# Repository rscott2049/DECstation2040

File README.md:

# DECstation 2040

## 1.0 Introduction

This document outlines the DECstation 2040, a RP2040 based DECstation 3000
emulator that can run DECWindows. A summary of features:

Hardware:

- RP2040, running at 1.8v/300 MHz
- 32 MB of PSRAM
- 8 MB SPI flash
- uSD card socket
- Monochrome VGA at 1024 x 864
- Ethernet RMII PHY support (socket on rev 1.5, integrated in rev 2.1)

Software:

- 4 port PSRAM PIO engine
- PIO driven VGA, with seperate 16x16 cursor plane overlay
- USB HID to DECWindows keyboard and mouse
  
## 1.1 Software 

### PIO:
The PSRAM/HyperRAM PIO engine provides 42/32 MB/s (write/read) of memory
bandwidth. Further, four PIO engines are used to provide four seperate
read/write memory ports. This allows independent memory access for
the emulated CPU, video DMA, and receive/send Ethernet traffic. Note that
all 32 instruction slots are used.

The video PIO engine can support up to a sysclk/2 pixel rate. Thus,
for the 300 MHz sysclk typically used, it is possible to run 1080p60 at
a pixel rate of 148.5 MHz. The default video rate is 1024 x 768 @ 70Hz,
as this matches the screen used for development and the pixel rate
is an integral divisor from sysclk. Only five PIO instruction slots are
used.

### DMA:
To drive the video PIO engine, five DMA channels are used. They are allocated
as follows:

- ctrl_dma_chan - points to DMA channel command packets
- data_dma_chan - executes DMA command packets
- ps_read_chan - points to PSRAM read data buffer
- inc_dma_chan - used to generate loop counter indices
- cur_inc_dma_chan - used as cursor loop counter

This project uses the RP2040 DMA sniffer to dynamically generate PSRAM
addresses, which eliminates the need to have a per-line PSRAM command packet. 
Further, it uses the inc_dma_chan to enable DMA command loops, eliminating
per-line DMA commands needed to send commands to the PIO pixel and PSRAM
PIO engines. This makes the amount of memory needed to drive video
independent of the display format. Currently, 86 DMA command packets are
used vs. approximately 2250 required for 1080p if a per-line DMA structure
was used.

In order to eliminate the latency from when the PSRAM PIO engine FIFO
has read data, and its delivery to SRAM, we use the ps_read_chan. This
channel is chained to after a PSRAM DMA command is executed. Without
this channel, the PSRAM PIO engine FIFO would be not be emptied until
the next DMA command is executed. This impacts the non-video PSRAM
channels, as they must wait unitl the video PSRAM command is complete.

### USB:
The USB HID code supports (at least) two keyboard/mouse combo types:
Rii mini X1 (model: RT-MWK01), purchased at MicroCenter, and Logitech
K830. 

### Emulator:
Dmitry's code at http://dmitry.gr/?r=05.Projects&proj=33.%20LinuxCard was
modified to support the RP2040, as well as adding support for video and USB
mouse/keyboard input. With overclocking and running the assembly language
version of the CPU emulator, Dmitry's Linux image reports a BOGOMIPS rating
of 13.44.

# 2.0) Getting started

## 2.1) Hardware
Build either rev 1.5 or 2.1, using the appropriate emu_brd directory. Please
note that rev 2.1 is still undergoing Ethernet debug, and has exhibited
significant packet drops. I use JLCPCB for board fabrication, and there are 
Digikey BOM spreadsheets in doc/bom. Recommend building two boards: one to
use as a 1.8v CMSIS debugger, and the other as the target. Feel free to only
populate the RP2040 related components on the CMSIS debugger.

The surface mount parts aren't too troublesome - I find the PSRAM BGA to be
much easier to solder than the RP2040 QFN. My technique is to use a hot-air
SMT rework tool. Recommended assembly steps:
1) Solder the voltage regulator, check for 1.8v and 3.3v when done.
2) Solder all of the passives, the RP2040, flash, and the USB connectors
if building rev 2.1. (Note that two bodge wires are needed to connect J5
and J11 D+/D- as my assumption that USB-A could serve as non-host connector
was incorrect).
When done, use blink_bringup (below) to check connections. (Edit blink.c
to enable the pins to check).
3) Solder the HyperRAM chip, run mem_test to check connections.
4) Solder the voltage translator chips, edit blink.c and run to check
connections.
5) Solder the connectors.

For rev 1.5:
Needs modified waveshare LAN8722 board. In addition to the modifications
outlined at: https://github.com/maximeborges/pico-rmii-ethernet, pin 13 of
the 7 x 2 connector (originally NC) is used as VDDIO for the LAN8722 chip.
To make this modification, cut the existing connection between LAN8722 pin
9 to 3.3v, and route pin 9 to pin 13 of the connector. This allows the use
of 1.8v I/O from the DECstation 2040 board. Also needed is a 6 pin header
to VGA connector. See rev 2.1 schematic for VGA pins needed.

## 2.2) Software
Start with:
http://dmitry.gr/?r=05.Projects&proj=33.%20LinuxCard
Download the images, particularly the ultrix.gui image. This should be placed
on a FAT32 for uMIPS. Edit uc_main.c to select which image to run.

Next, go to where this README.md is stored. Then set current directory to sw.
Edit the "source_this" file to reflect the location of the Pico SDK, and source
this file to set the PICO_SDK environment variable for the current session.

A good place to start is with the blink_bringup directory. CD to this,
and do:

`cmake -B build -S .`

Build software via

`./build.sh`

This will generate an .elf file in build/src. Use picotool to load this onto
the target board. After rebooting, should get "hello, world" on USB serial, as
well as on the hardware serial port. A 500 Hz square wave should be present
on GPIO21 (ret_clk). This can be changed via editing the src/blink.c file.
I use this tool incrementally while soldering the board, to verify connectivity.

Next, build the CMSIS debugger. CD to the picoprobe directory and
build with:

`cmake -B build -DCUSTOMPROBE=1
make -C build`

Program with

`sudo picotool load build/customprobe.elf`

Now go to the psram directory and do:

`cmake -B build -S .`

Build software via

`./build.sh`

This will generate most of the available packages. Of interest are:

- mem_test - a simple memory tester
- fb_test - test program for the frame buffer library
- fb_mem_test - memory test with frame buffer enabled
- pico-rv32ima - RISC-V linux emulation
- uMIPS - DECstation emulation
- pico_rmii_ethernet_httpd - test program for RMII. 

There are shell scripts to load the above:

- cl_sram.sh   - sd command line
- eth_sram.sh  - ethernet test
- fb_flash.sh  - framebuffer library test, run from flash
- fb_sram.sh   - framebuffer library test, run from SRAM
- fbm_flash.sh - memory test with framebuffer enabled, run from flash
- fbm_sram.sh  - memory test with framebuffer enabled, run from SRAM
- mt_sram.sh   - memory test, run from SRAM
- mt_flash.sh  - memory test, run from flash
- um_flash.sh - uMIPS emulator, run from flash
- um_sram.sh  - uMIPS emulator, run from SRAM

Running the code:
Connect the debugger board to the SWD port on the target.
Start the CMSIS debugger via sw/start_cmsis.sh.
Execute one of the scripts above. This will load the program into RP2040
SRAM and start it.

If you wish to run from flash, comment out the no_flash line in the source CMakeLists.txt. Note that the uMIPS emulator requires "copy_to_ram" to be enabled
when running from flash.

# 3.0) Commentary

This project has been a voyage of discovery. The first doc/build_log.txt entry
was on 23-mar-2023, but I'd been thinking of building a business card
ever since I'd read Dmitry's LinuxCard web page. I've learned how to
use the RP2040 PIO engines and the DMA subsystem to push pixels. I'm
amazed at how flexible and capable the RP2040 has turned out to be. Hats off
to the RP2040 designers! 

Most enjoyable moments:

- When the PSRAM PIO engine finally ran the memory test overnight.
- When the second solution to the problem of how to get the DMA subsytem
to do a counted loop actually worked without killing SD card access.
- When the DMA cursor read data during blanking worked, giving smooth
cursor movement.

Less than enjoyable moments:

- Realizing the "optimization" of reordering data on the PSRAM to improve
layout was wrong, after submitting the design to JLCPCB.
-  Realizing that the first flash part chosen didn't support "Continuous Read
Mode". On the other hand, this did force me to learn how to do SRAM builds,
speeding up development.
- Having the wrong footprint for the level translator on rev 1.3.
- Finding out that Digikey no longer stocked the Ethernet connector on
rev 2.0, after submitting PCB. Related - the PSRAM was out of stock, so
clicked on the recommended alternative. Was disappointed when the box
showed up, and it was the waferscale part. Tiny, but unsolderable.

# 4.0) Next steps
- Use the ps_get_buf DMA subroutine to setup the cursor PSRAM command. This
will reduce the memory footprint.
- Write the lance Ethernet emulation code for uMIPS.
- Port MicroMac https://axio.ms/projects/2024/06/16/MicroMac.html

# 5.0) Acknowledgements

This project would not exist without Dmitry's excellent LinuxCard project,
at: http://dmitry.gr/?r=05.Projects&proj=33.%20LinuxCard

Inspiration and software framework:
https://github.com/Wren6991/PicoDVI.git

DEC mouse and keyboard support used code from:
https://hackaday.io/project/19576-dec-mouse-adapter and 
https://github.com/pkoning2/lk201emu.git

Ethernet:
https://github.com/maximeborges/pico-rmii-ethernet

Also, Hackaday.com for articles on SMT soldering, USB-C, etc., giving me
confidence that I could actually do this project!

## Pictures/video
A selection of pictures from doc/photos follows. See doc/photos for pictures
of previous versions and how the emulated video output progressed from first
pixel to current.
### Video showing [Xmaze/worms](https://youtu.be/O6Lyjsey6ek) running
### 
Rev 1.5
### 
Rev 1.5 running
### 
Rev 2.1
### 
Rev 2.1 running with Logitech keyboard
### 
Helper cat in the parts box

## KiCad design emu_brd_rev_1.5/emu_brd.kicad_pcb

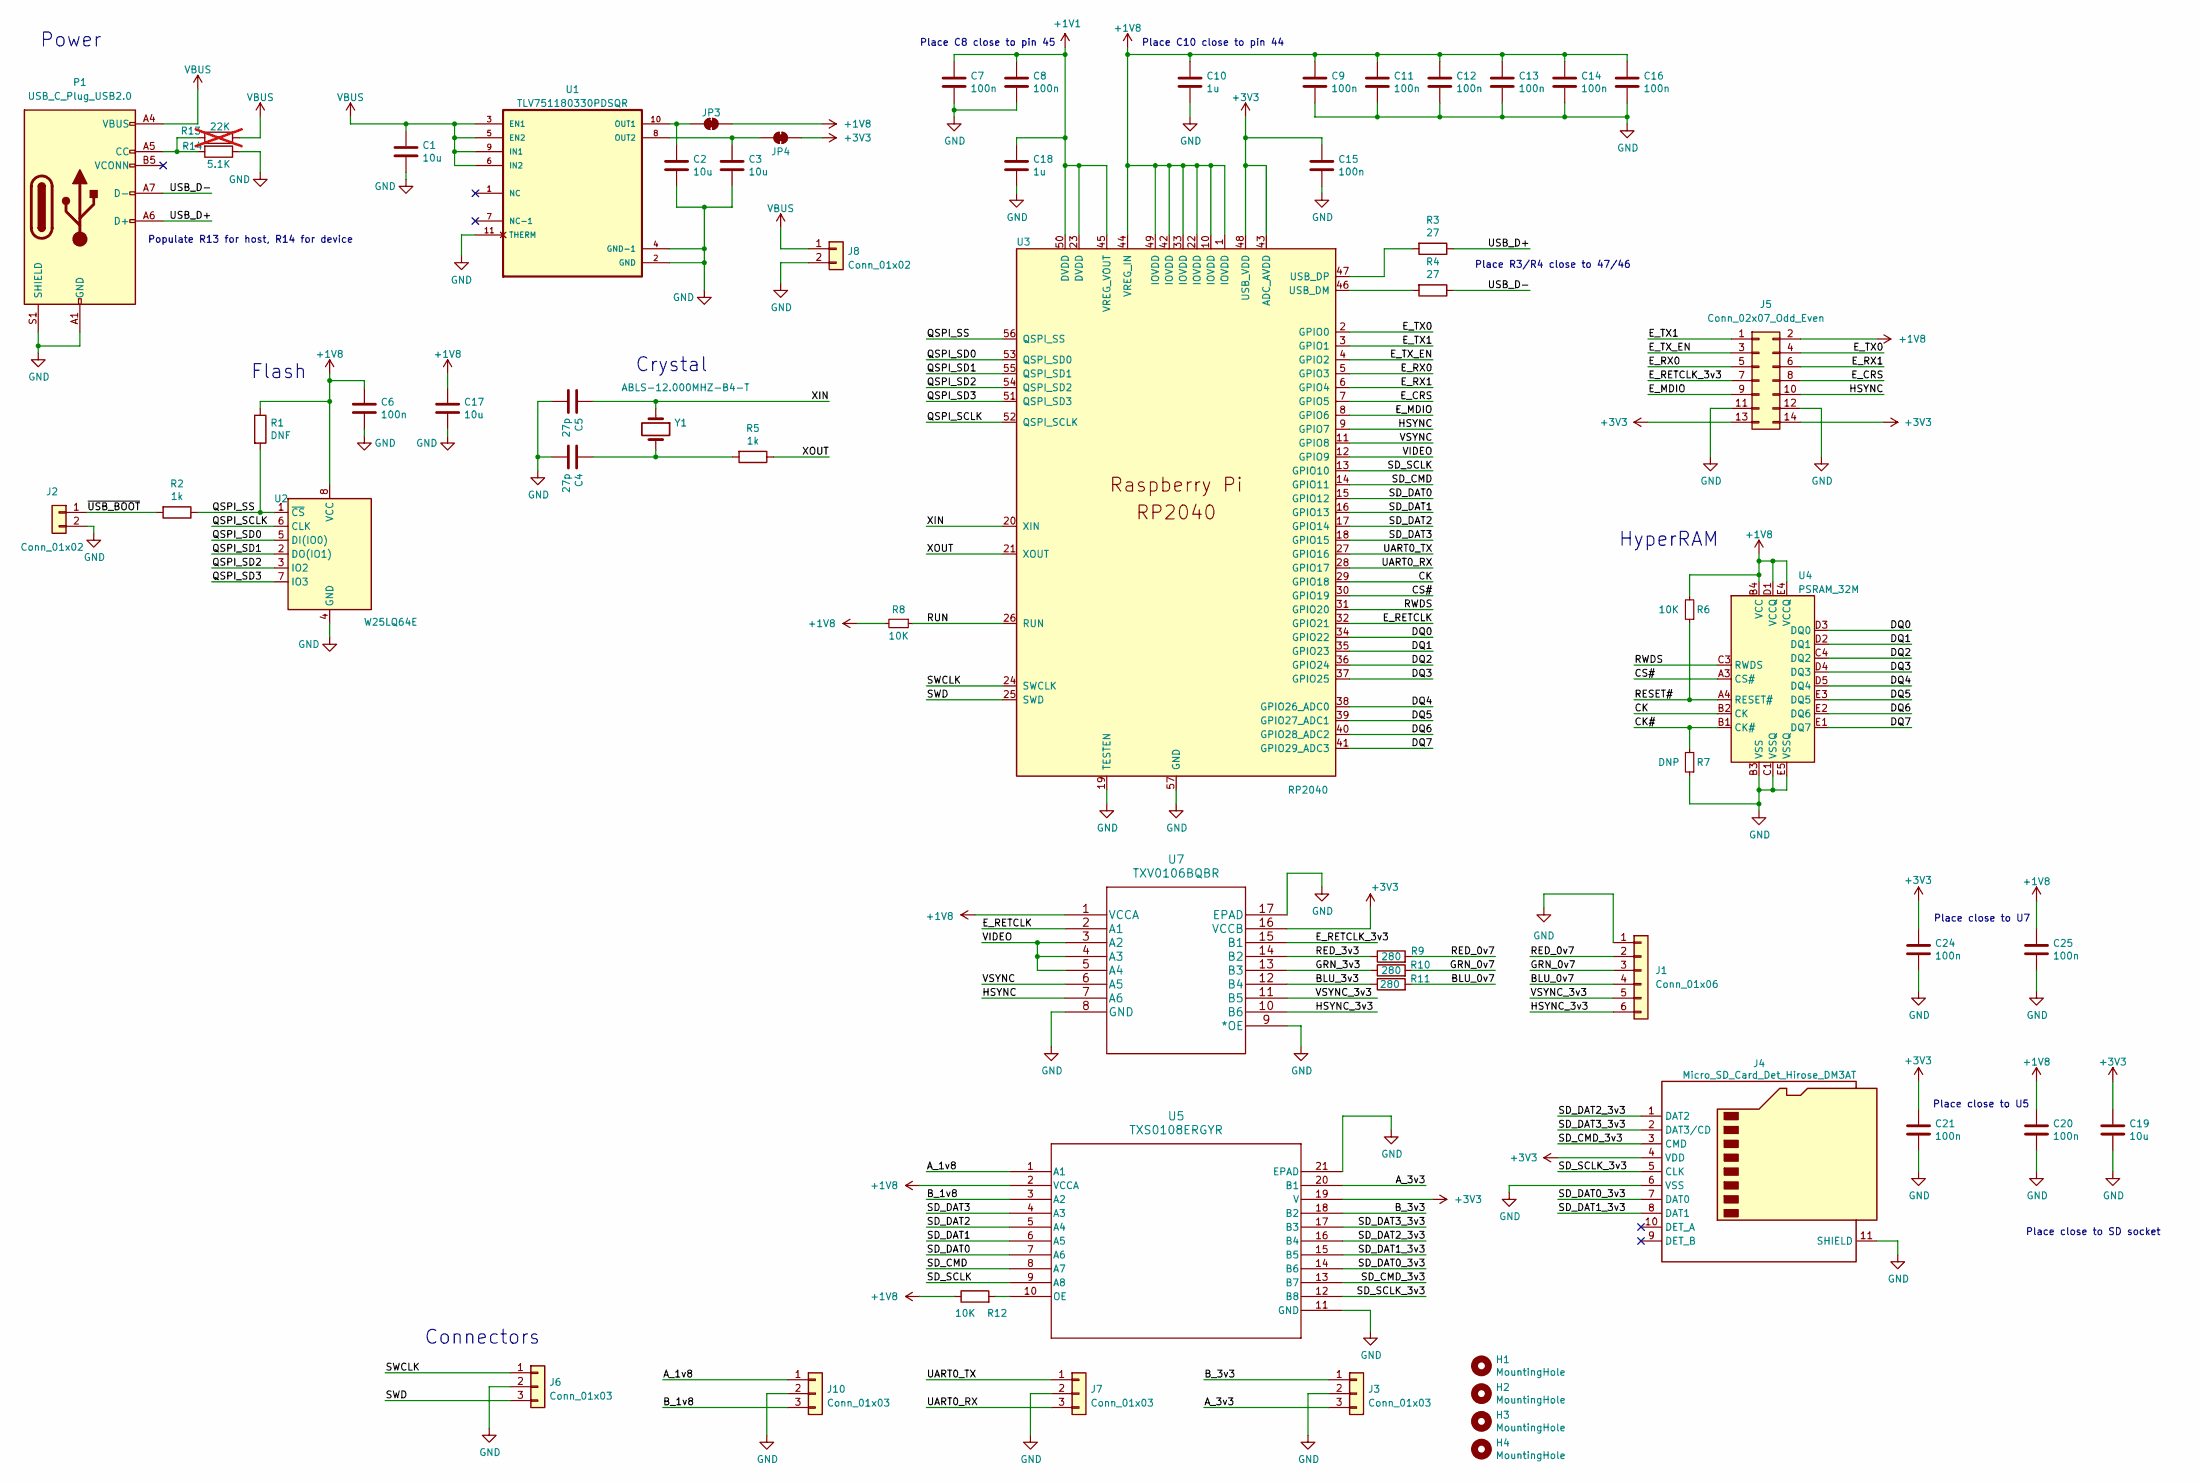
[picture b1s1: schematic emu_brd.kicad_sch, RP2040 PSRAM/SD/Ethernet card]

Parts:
C1, C2, C3, C17, C19: 10u; C_0805_2012Metric
C4, C5: 27p; C_0603_1608Metric
C6, C7, C8, C9, C11, C12, C13, C14, C15, C16, C20, C21, C24, C25: 100n; C_0603_1608Metric
C10, C18: 1u; C_0603_1608Metric
H1, H2, H3, H4: MountingHole; MountingHole_2.7mm_M2.5
J1: Conn_01x06; PinHeader_1x06_P2.54mm_Vertical
J2, J8: Conn_01x02; PinHeader_1x02_P2.54mm_Vertical
J3, J6, J7, J10: Conn_01x03; PinHeader_1x03_P2.54mm_Vertical
J4: Micro_SD_Card_Det_Hirose_DM3AT; microSD_HC_Hirose_DM3D-SF
J5: Conn_02x07_Odd_Even; PinSocket_2x07_P2.54mm_Horizontal
JP3, JP4: SolderJumper_2_Bridged; SolderJumper-2_P1.3mm_Bridged_Pad1.0x1.5mm
P1: USB_C_Plug_USB2.0; PCB-USB-C
R1: DNF; C_0603_1608Metric
R2, R5: 1k; C_0603_1608Metric
R3, R4: 27; C_0603_1608Metric
R6, R8, R12: 10K; R_0603_1608Metric
R7: DNP; R_0603_1608Metric
R9, R10, R11: 280; R_0603_1608Metric
R13: 22K; R_0603_1608Metric; not fitted
R14: 5.1K; R_0603_1608Metric
U1: TLV751180330PDSQR; SON40P200X200X80-11N
U2: W25LQ64E; WIN_ZP-8_WIN
U3: RP2040; RP2040-QFN-56
U4: PSRAM_32M; BGA25C100P5X5_800X600X120N
U5: TXS0108ERGYR; RGY20_3P05X2P05
U7: TXV0106BQBR; DHVQFN-16-1EP_2.5x3.5mm_P0.5mm_EP1x2mm
Y1: ABLS-12.000MHZ-B4-T; Crystal_SMD_5032-2Pin_5.0x3.2mm_HandSoldering

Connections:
+1V1: C7.1, C8.1, C18.1, U3.23 (DVDD), U3.45 (VREG_VOUT), U3.50 (DVDD)
+1V8: C6.1, C9.1, C10.1, C11.1, C12.1, C13.1, C14.1, C16.1, C17.1, C20.1, C25.1, J5.2, JP3.2 (B), R1.1, R6.2, R8.2, R12.1, U2.8 (VCC), U3.1 (IOVDD), U3.10 (IOVDD), U3.22 (IOVDD), U3.33 (IOVDD), U3.42 (IOVDD), U3.44 (VREG_IN), U3.49 (IOVDD), U4.B4 (VCC), U4.D1 (VCCQ), U4.E4 (VCCQ), U5.2 (VCCA), U7.1 (VCCA)
+3V3: C15.1, C19.1, C21.1, C24.1, J4.4 (VDD), J5.13, J5.14, JP4.2 (B), U3.43 (ADC_AVDD), U3.48 (USB_VDD), U5.19 (V), U7.16 (VCCB)
/A_1v8: J10.1, U5.1 (A1)
/A_3v3: J3.3, U5.20 (B1)
/BLU_0v7: J1.4, R11.2
/BLU_3v3: R11.1, U7.12 (B4)
/B_1v8: J10.3, U5.3 (A2)
/B_3v3: J3.1, U5.18 (B2)
/CK: U3.29 (GPIO18), U4.B2 (CK)
/CK#: R7.2, U4.B1 (CK#)
/CS#: U3.30 (GPIO19), U4.A3 (CS#)
/DQ0: U3.34 (GPIO22), U4.D3 (DQ0)
/DQ1: U3.35 (GPIO23), U4.D2 (DQ1)
/DQ2: U3.36 (GPIO24), U4.C4 (DQ2)
/DQ3: U3.37 (GPIO25), U4.D4 (DQ3)
/DQ4: U3.38 (GPIO26_ADC0), U4.D5 (DQ4)
/DQ5: U3.39 (GPIO27_ADC1), U4.E3 (DQ5)
/DQ6: U3.40 (GPIO28_ADC2), U4.E2 (DQ6)
/DQ7: U3.41 (GPIO29_ADC3), U4.E1 (DQ7)
/E_CRS: J5.8, U3.7 (GPIO5)
/E_MDIO: J5.9, U3.8 (GPIO6)
/E_RETCLK: U3.32 (GPIO21), U7.2 (A1)
/E_RETCLK_3v3: J5.7, U7.15 (B1)
/E_RX0: J5.5, U3.5 (GPIO3)
/E_RX1: J5.6, U3.6 (GPIO4)
/E_TX0: J5.4, U3.2 (GPIO0)
/E_TX1: J5.1, U3.3 (GPIO1)
/E_TX_EN: J5.3, U3.4 (GPIO2)
/GRN_0v7: J1.3, R10.2
/GRN_3v3: R10.1, U7.13 (B3)
/HSYNC: J5.10, U3.9 (GPIO7), U7.7 (A6)
/HSYNC_3v3: J1.6, U7.10 (B6)
/QSPI_SCLK: U2.6 (CLK), U3.52 (QSPI_SCLK)
/QSPI_SD0: U2.5 (DI(IO0)), U3.53 (QSPI_SD0)
/QSPI_SD1: U2.2 (DO(IO1)), U3.55 (QSPI_SD1)
/QSPI_SD2: U2.3 (IO2), U3.54 (QSPI_SD2)
/QSPI_SD3: U2.7 (IO3), U3.51 (QSPI_SD3)
/QSPI_SS: R1.2, R2.1, U2.1 (~CS), U3.56 (QSPI_SS)
/RED_0v7: J1.2, R9.2
/RED_3v3: R9.1, U7.14 (B2)
/RESET#: R6.1, U4.A4 (RESET#)
/RUN: R8.1, U3.26 (RUN)
/RWDS: U3.31 (GPIO20), U4.C3 (RWDS)
/SD_CMD: U3.14 (GPIO11), U5.8 (A7)
/SD_CMD_3v3: J4.3 (CMD), U5.13 (B7)
/SD_DAT0: U3.15 (GPIO12), U5.7 (A6)
/SD_DAT0_3v3: J4.7 (DAT0), U5.14 (B6)
/SD_DAT1: U3.16 (GPIO13), U5.6 (A5)
/SD_DAT1_3v3: J4.8 (DAT1), U5.15 (B5)
/SD_DAT2: U3.17 (GPIO14), U5.5 (A4)
/SD_DAT2_3v3: J4.1 (DAT2), U5.16 (B4)
/SD_DAT3: U3.18 (GPIO15), U5.4 (A3)
/SD_DAT3_3v3: J4.2 (DAT3/CD), U5.17 (B3)
/SD_SCLK: U3.13 (GPIO10), U5.9 (A8)
/SD_SCLK_3v3: J4.5 (CLK), U5.12 (B8)
/SWCLK: J6.1, U3.24 (SWCLK)
/SWD: J6.3, U3.25 (SWD)
/UART0_RX: J7.3, U3.28 (GPIO17)
/UART0_TX: J7.1, U3.27 (GPIO16)
/USB_D+: P1.A6 (D+), R3.1
/USB_D-: P1.A7 (D-), R4.1
/VIDEO: U3.12 (GPIO9), U7.3 (A2), U7.4 (A3), U7.5 (A4)
/VSYNC: U3.11 (GPIO8), U7.6 (A5)
/VSYNC_3v3: J1.5, U7.11 (B5)
/XIN: C5.1, U3.20 (XIN), Y1.1
/XOUT: R5.1, U3.21 (XOUT)
/~USB_BOOT: J2.1, R2.2
GND: C1.2, C2.2, C3.2, C4.2, C5.2, C6.2, C7.2, C8.2, C9.2, C10.2, C11.2, C12.2, C13.2, C14.2, C15.2, C16.2, C17.2, C18.2, C19.2, C20.2, C21.2, C24.2, C25.2, J1.1, J2.2, J3.2, J4.6 (VSS), J4.11 (SHIELD), J5.11, J5.12, J6.2, J7.2, J8.2, J10.2, P1.A1 (GND), P1.A12 (GND), P1.B1 (GND), P1.B12 (GND), P1.S1 (SHIELD), R7.1, R14.1, U1.2 (GND), U1.4 (GND-1), U1.11 (THERM), U2.4 (GND), U2.9, U3.19 (TESTEN), U3.57 (GND), U4.B3 (VSS), U4.C1 (VSSQ), U4.E5 (VSSQ), U5.11 (GND), U5.21 (EPAD), U7.8 (GND), U7.9 (*OE), U7.17 (EPAD)
unnamed: C4.1, R5.2, Y1.2
unnamed: C2.1, JP3.1 (A), U1.10 (OUT1)
unnamed: C3.1, JP4.1 (A), U1.8 (OUT2)
unnamed: P1.A5 (CC), R13.2, R14.2
unnamed: R4.2, U3.46 (USB_DM)
unnamed: R3.2, U3.47 (USB_DP)
unnamed: R12.2, U5.10 (OE)
VBUS: C1.1, J8.1, P1.A4 (VBUS), P1.A9 (VBUS), P1.B4 (VBUS), P1.B9 (VBUS), R13.1, U1.3 (EN1), U1.5 (EN2), U1.6 (IN2), U1.9 (IN1)

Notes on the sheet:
Connectors
Place close to SD socket
Flash
Place R3/R4 close to 47/46
Power
Place close to U5
Place C8 close to pin 45
HyperRAM
Populate R13 for host, R14 for device
Crystal
Place C10 close to pin 44
Place close to U7

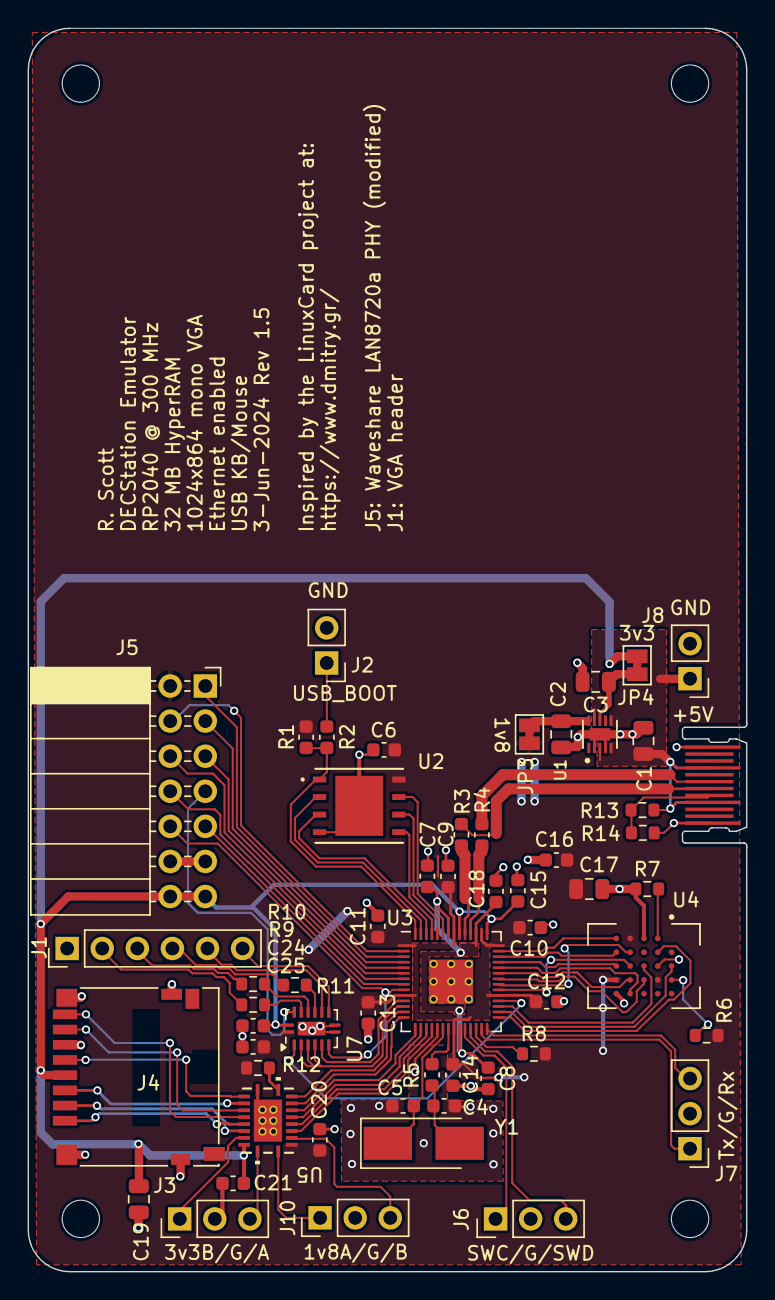
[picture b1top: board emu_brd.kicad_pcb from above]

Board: 2 copper layers, 52.0 x 90.0 mm, 60 parts (0 on the bottom side), 77 nets.

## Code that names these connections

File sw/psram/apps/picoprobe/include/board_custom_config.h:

/*
 * The MIT License (MIT)
 *
 * Copyright (c) 2023 Raspberry Pi (Trading) Ltd.
 *
 * Permission is hereby granted, free of charge, to any person obtaining a copy
 * of this software and associated documentation files (the "Software"), to deal
 * in the Software without restriction, including without limitation the rights
 * to use, copy, modify, merge, publish, distribute, sublicense, and/or sell
 * copies of the Software, and to permit persons to whom the Software is
 * furnished to do so, subject to the following conditions:
 *
 * The above copyright notice and this permission notice shall be included in
 * all copies or substantial portions of the Software.
 *
 * THE SOFTWARE IS PROVIDED "AS IS", WITHOUT WARRANTY OF ANY KIND, EXPRESS OR
 * IMPLIED, INCLUDING BUT NOT LIMITED TO THE WARRANTIES OF MERCHANTABILITY,
 * FITNESS FOR A PARTICULAR PURPOSE AND NONINFRINGEMENT. IN NO EVENT SHALL THE
 * AUTHORS OR COPYRIGHT HOLDERS BE LIABLE FOR ANY CLAIM, DAMAGES OR OTHER
 * LIABILITY, WHETHER IN AN ACTION OF CONTRACT, TORT OR OTHERWISE, ARISING FROM,
 * OUT OF OR IN CONNECTION WITH THE SOFTWARE OR THE USE OR OTHER DEALINGS IN
 * THE SOFTWARE.
 *
 */

#ifndef BOARD_CUSTOM_H_
#define BOARD_CUSTOM_H_

/* Direct connection - SWCLK/SWDIO on two GPIOs */
#define PROBE_IO_RAW

/* Include CDC interface to bridge to target UART. Omit if not used. */
#define PROBE_CDC_UART

#define PROBE_SM 0
// Use emu board 3v3 I/Os for SWD: J7, select GPIO16/17 via jumpers 1 & 2
//#define PROBE_PIN_OFFSET 16

// Use emu board 3v3 I/Os for SWD: GPIO13/14 (aka: SD_CMD1, SD_CMD2)
//#define PROBE_PIN_OFFSET 13

// Use emu board 1v8 I/Os for SWD: GPIO8/9
#define PROBE_PIN_OFFSET 8

/* PIO config for PROBE_IO_RAW */
#if defined(PROBE_IO_RAW)
#define PROBE_PIN_SWCLK (PROBE_PIN_OFFSET + 0)
#define PROBE_PIN_SWDIO (PROBE_PIN_OFFSET + 1)
#endif

#if defined(PROBE_CDC_UART)
#define PICOPROBE_UART_TX 16
#define PICOPROBE_UART_RX 17

#define PICOPROBE_UART_INTERFACE uart0
#define PICOPROBE_UART_BAUDRATE 115200
#endif

/* LED config - some or all of these can be omitted if not used */
//#define PICOPROBE_USB_CONNECTED_LED 2
//#define PICOPROBE_DAP_CONNECTED_LED 15
//#define PICOPROBE_DAP_RUNNING_LED 16
//#define PICOPROBE_UART_RX_LED 7
//#define PICOPROBE_UART_TX_LED 8

#define PROBE_PRODUCT_STRING "Custom board as Pico Probe"

#endif

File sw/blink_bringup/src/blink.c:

/**
 * LED blink test
 */

#include <stdio.h>
#include "pico/stdlib.h"
#include "hardware/interp.h"

// Test pins for input
//#define INPUT
// Which pin to use for stimulus output
// J5, pin 6 - HSYNC pin on rev 1.3 and above
#define TOGGLE_PIN 7

// Test output only
#define OUTPUT
// Just run with blink delays, but no pins
//uint LED_PIN = 0;
//uint NUM_PINS = 0;

// Random pin testing
//uint LED_PIN = 13;
//uint NUM_PINS = 2;

// Test the SD GPIOs
//uint LED_PIN = 10;
//uint NUM_PINS = 6;

// Test the Enet GPIOs (except for RETCLK)
//uint LED_PIN = 0;
//uint NUM_PINS = 8;

// Test RETCLK
uint LED_PIN = 21;
uint NUM_PINS = 1;

// Test UART pins
//uint LED_PIN = 16;
//uint NUM_PINS = 2;

// Test video header pins
//uint LED_PIN = 7;
//uint NUM_PINS = 3;

// Test J6 header GPIO pins
//uint LED_PIN = 8;
//uint NUM_PINS = 2;


// Test PSRAM data pins
//uint LED_PIN = 22;
//uint NUM_PINS = 8;

// Test PSRAM ctl pins
//uint LED_PIN = 18;
//uint NUM_PINS = 3;

// Test all pins (no PSRAM installed)
//uint LED_PIN = 0;
//uint NUM_PINS = 30;


void setup() {
  for (int i = 0; i < NUM_PINS; i++) {
    gpio_init(LED_PIN + i);
    gpio_set_dir(LED_PIN + i, GPIO_OUT);
  }
}

void input_setup() {
  gpio_init(TOGGLE_PIN);
  gpio_set_dir(TOGGLE_PIN, GPIO_OUT);

  for (int i = 0; i < NUM_PINS; i++) {
    gpio_init(LED_PIN + i);
    gpio_set_dir(LED_PIN + i, GPIO_IN);
    gpio_set_pulls(LED_PIN + i, false, true);
  }
}


void blink() {
  for (int i = 0; i < NUM_PINS; i++) {
      gpio_put(LED_PIN + i, i & 1);
  }
  sleep_ms(1);
  for (int i = 0; i < NUM_PINS; i++) {
    gpio_put(LED_PIN + i, !(i & 1));
  }
  sleep_ms(1);
}

uint32_t input_scan() {
  uint32_t result_one = 0;
  uint32_t result_zero = 0;

  // Set stimulus pin
  gpio_put(TOGGLE_PIN, 1);
  sleep_ms(1);
  for (int i = 0; i < NUM_PINS; i++) {
    result_one |= (gpio_get(LED_PIN + i) & 0x01) << i;
  }

  // Clear stimulus pin
  gpio_put(TOGGLE_PIN, 0);
  sleep_ms(1);
  for (int i = 0; i < NUM_PINS; i++) {
    result_zero |= (!gpio_get(LED_PIN + i) & 0x01) << i;
  }

  //  return (result_one & result_zero);
  return(result_one);
}
 
int main() {
  uint32_t tick;
  uint32_t count = 0;

  stdio_init_all();
  sleep_ms(1000);

#ifdef OUTPUT
  setup();
  tick = 500;

  while (1) {
    blink();
    if (--tick == 0) {
      printf("Hello, world! %08x\n", count++);
      tick = 500;
    }
  }
#endif

#ifdef INPUT
  uint32_t results = 0;

  printf("Input testing, starting at pin: %d\n", LED_PIN);
  input_setup();
  tick = 250;

  while (1) {
    results = input_scan();
    if (--tick == 0) {
      if (results) {
	printf("%08d Results: %08x\n", count++, results);
	tick = 250;
      }
    }
  }
#endif


  return 0;
}

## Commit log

2024-07-01 Minor edits
2024-07-20 Fix rev 2.1 photo
